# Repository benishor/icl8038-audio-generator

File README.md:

# icl8038-audio-generator

A KiCad realisation of Thomas Henry's 8038 audio generator project.
As this project uses a custom library, use `git clone --recursive` in order to bring all submodules.

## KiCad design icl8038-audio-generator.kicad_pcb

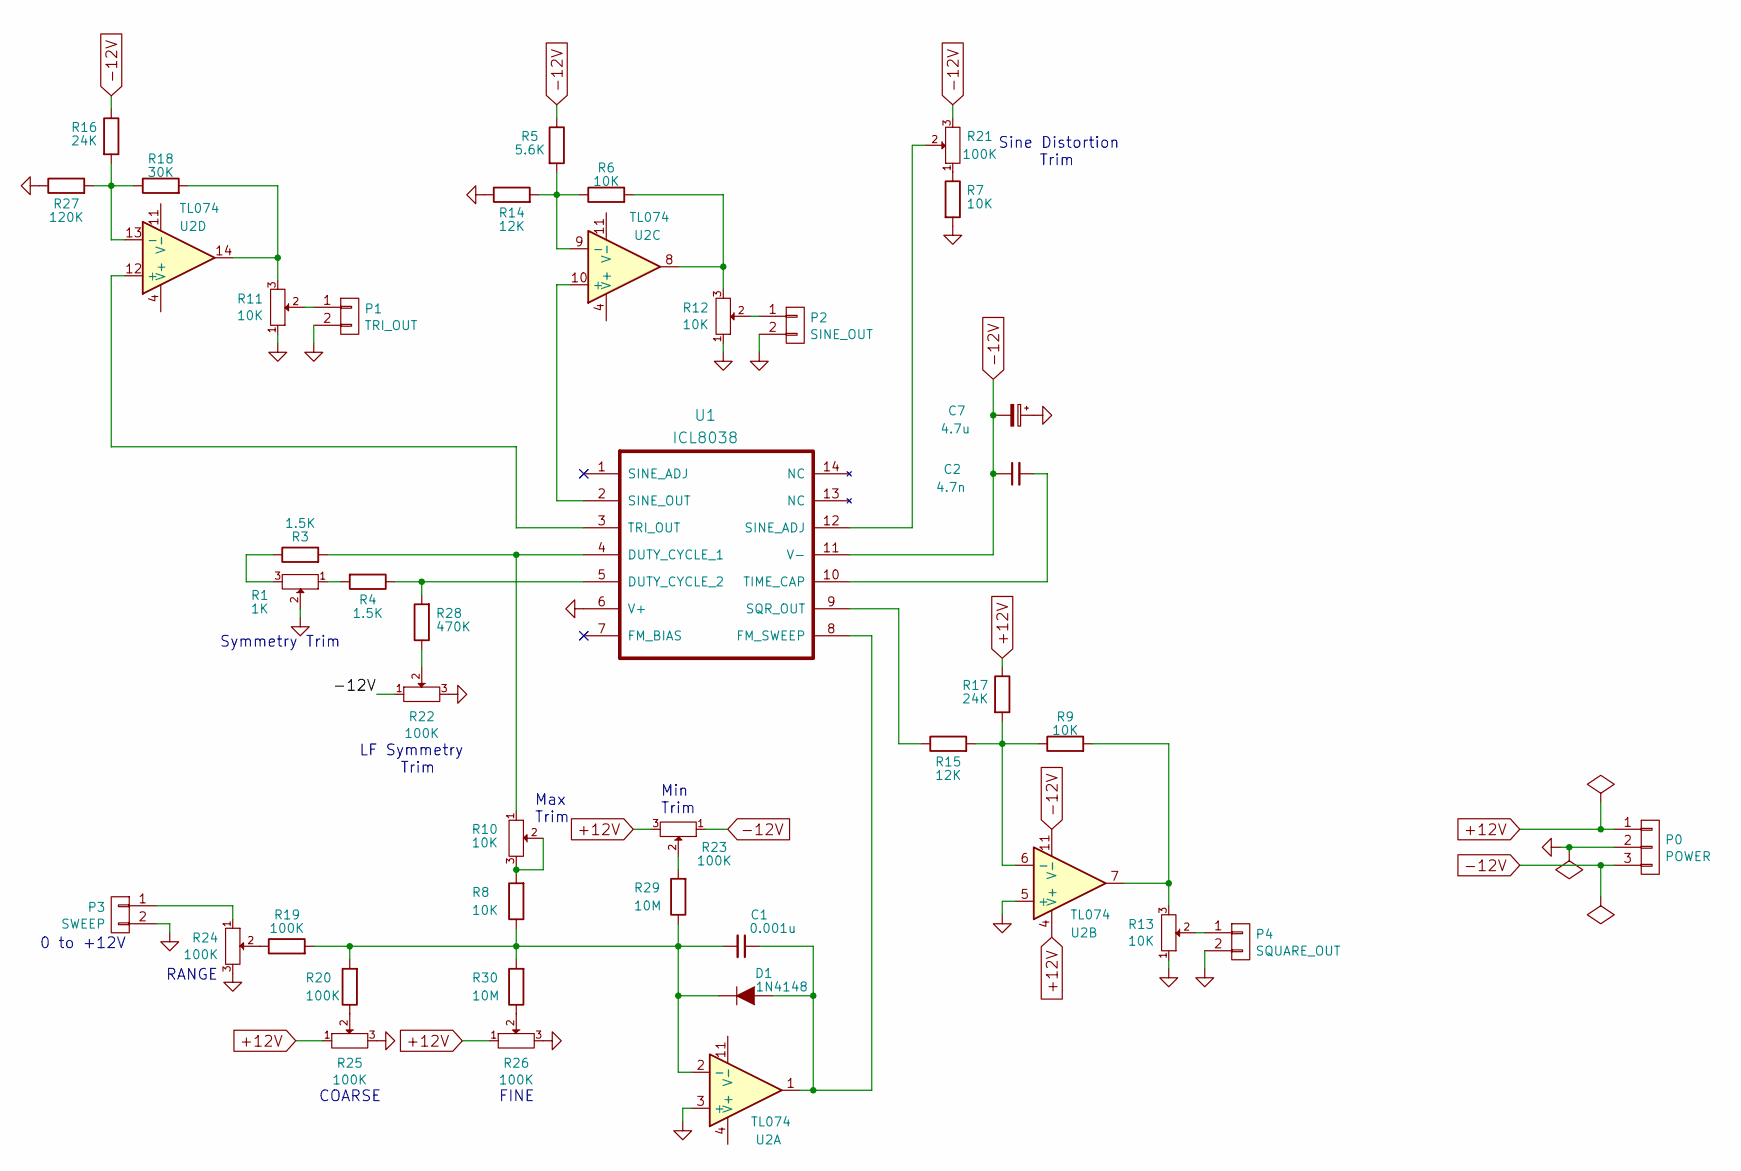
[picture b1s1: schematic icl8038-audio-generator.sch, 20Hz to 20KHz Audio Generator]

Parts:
C1: 0.001u; C_Disc_D7.5_P5
C2: 4.7n; C_Disc_D7.5_P5
C7: 4.7u; C_Radial_D5_L6_P2.5
D1: 1N4148; Diode_DO-35_SOD27_Horizontal_RM10
P0: POWER; Pin_Header_Straight_1x03
P1: TRI_OUT; Pin_Header_Straight_1x02
P2: SINE_OUT; Pin_Header_Straight_1x02
P3: SWEEP; Pin_Header_Straight_1x02
P4: SQUARE_OUT; Pin_Header_Straight_1x02
R1: 1K; Potentiometer_Bourns_3296W_3-8Zoll_Inline_ScrewUp
R3, R4: 1.5K; Resistor_Horizontal_RM10mm
R5: 5.6K; Resistor_Horizontal_RM10mm
R6, R7, R8, R9: 10K; Resistor_Horizontal_RM10mm
R10: 10K; Potentiometer_Bourns_3296W_3-8Zoll_Inline_ScrewUp
R11, R12, R13: 10K; Pin_Header_Straight_1x03
R14, R15: 12K; Resistor_Horizontal_RM10mm
R16, R17: 24K; Resistor_Horizontal_RM10mm
R18: 30K; Resistor_Horizontal_RM10mm
R19, R20: 100K; Resistor_Horizontal_RM10mm
R21, R22, R23: 100K; Potentiometer_Bourns_3296W_3-8Zoll_Inline_ScrewUp
R24, R25, R26: 100K; Pin_Header_Straight_1x03
R27: 120K; Resistor_Horizontal_RM10mm
R28: 470K; Resistor_Horizontal_RM10mm
R29, R30: 10M; Resistor_Horizontal_RM10mm
U1: ICL8038; DIP-14_W7.62mm_LongPads
U2: TL074; DIP-14_W7.62mm_LongPads

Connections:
+12V: P0.1, R17.1, R23.3, R25.1, R26.1, U2.4 (V+)
-12V: C2.1, C7.2, P0.3, R5.1, R16.1, R21.3, R22.1, R23.1, U1.11 (V-), U2.11 (V-)
GND: C7.1, P0.2, P1.2, P2.2, P3.2, P4.2, R1.2, R7.2, R11.1, R12.1, R13.1, R14.1, R22.3, R24.3, R25.3, R26.3, R27.1, U1.6 (V+), U2.3 (+), U2.5 (+)
unnamed: C1.1, D1.2 (A), U1.8 (FM_SWEEP), U2.1
unnamed: C1.2, D1.1 (K), R8.1, R19.2, R20.2, R29.1, R30.2, U2.2 (-)
unnamed: C2.2, U1.10 (TIME_CAP)
unnamed: P1.1, R11.2
unnamed: P2.1, R12.2
unnamed: P3.1, R24.1
unnamed: P4.1, R13.2
unnamed: R1.1, R4.2
unnamed: R1.3, R3.1
unnamed: R3.2, R10.1, U1.4 (DUTY_CYCLE_1)
unnamed: R8.2, R10.2, R10.3
unnamed: R11.3, R18.2, U2.14
unnamed: R6.2, R12.3, U2.8
unnamed: R9.2, R13.3, U2.7
unnamed: R5.2, R6.1, R14.2, U2.9 (-)
unnamed: R15.1, U1.9 (SQR_OUT)
unnamed: R9.1, R15.2, R17.2, U2.6 (-)
unnamed: R16.2, R18.1, R27.2, U2.13 (-)
unnamed: R19.1, R24.2
unnamed: R20.1, R25.2
unnamed: R7.1, R21.1
unnamed: R21.2, U1.12 (SINE_ADJ)
unnamed: R22.2, R28.1
unnamed: R23.2, R29.2
unnamed: R26.2, R30.1
unnamed: R4.1, R28.2, U1.5 (DUTY_CYCLE_2)
unnamed: U1.2 (SINE_OUT), U2.10 (+)
unnamed: U1.3 (TRI_OUT), U2.12 (+)

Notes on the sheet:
0 to +12V
RANGE
COARSE
FINE
LF Symmetry Trim
Symmetry Trim
Sine Distortion Trim
Max Trim
Min Trim

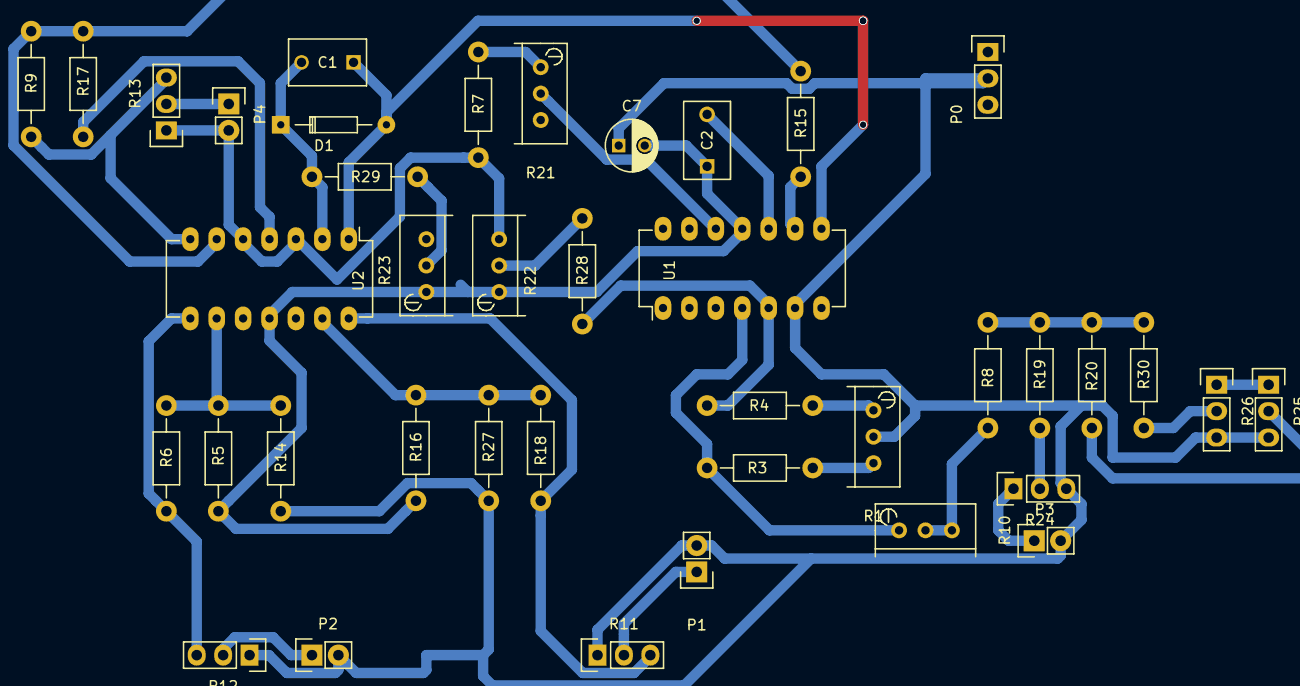
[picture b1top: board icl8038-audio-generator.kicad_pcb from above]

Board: 2 copper layers, 40 parts (0 on the bottom side), 31 nets.

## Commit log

2016-10-09 Initial import. Schematic done but PCB is WIP
2016-10-09 Updated library dependency

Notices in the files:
icl8038-audio-generator.sch:
(c) 2007 Thomas Henry
